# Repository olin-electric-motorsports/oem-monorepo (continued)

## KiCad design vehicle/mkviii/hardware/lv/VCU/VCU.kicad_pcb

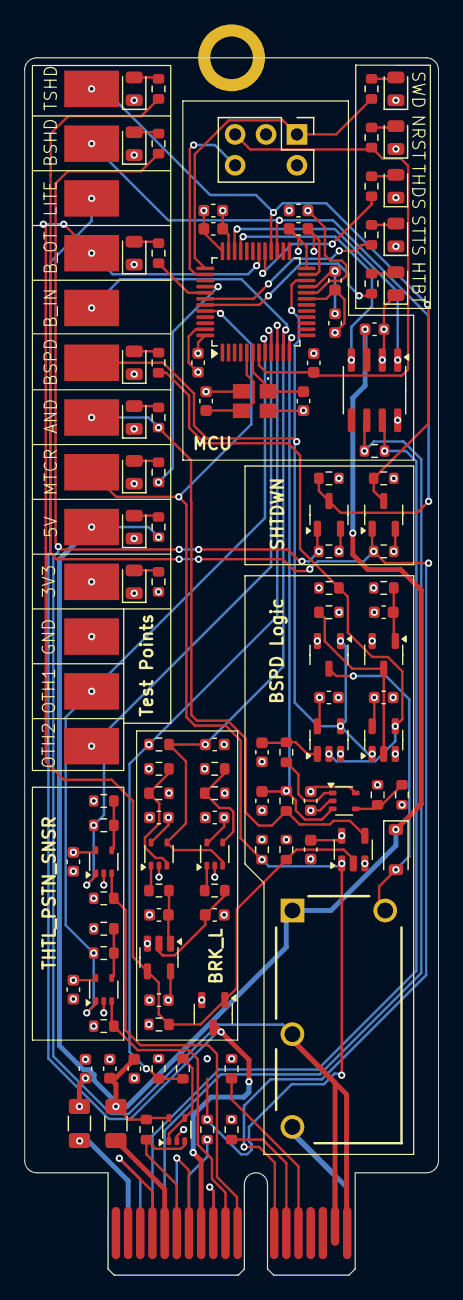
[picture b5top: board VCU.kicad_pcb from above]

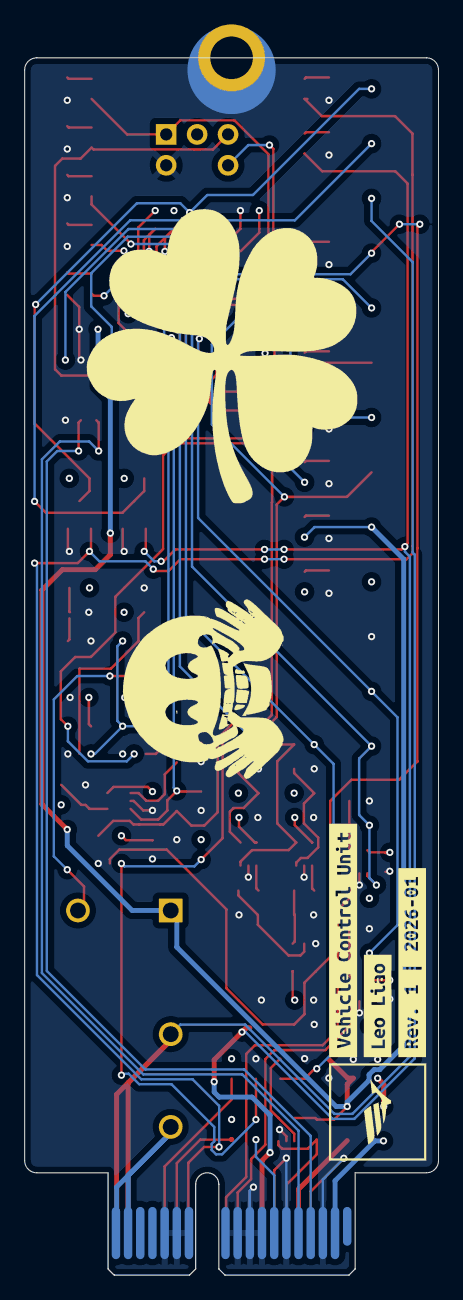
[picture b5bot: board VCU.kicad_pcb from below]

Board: 4 copper layers, 34.0 x 100.0 mm, 130 parts (3 on the bottom side), 69 nets.

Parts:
C1, C3, C5, C7, C9, C14, C15, C17, C19, C20, C21, C23, C24, C27, C28, C29: C_0.1uF; C_0603_1608Metric
C2: C_10nF; C_0603_1608Metric
C4, C18: C_1uF; C_0603_1608Metric
C6: C_4.7uF; C_0603_1608Metric
C8, C10: C_30pF; C_0603_1608Metric
C11, C26: C_0.1uF_16V; C_0603_1608Metric
C12, C13, C16: C_10uF_10V; C_0603_1608Metric
C22: C_0.22uF_50V; C_0603_1608Metric
C25: C_1uF_25V; C_0603_1608Metric
D1: MOTOR_ON; D_0805_2012Metric
D2: BRAKES; D_0805_2012Metric
D3: BSPD_TRIP; D_0805_2012Metric
D4: HEARTBEAT; D_0805_2012Metric
D5: THROTTLE_DISABLE; D_0805_2012Metric
D6: 5V; D_0805_2012Metric
D7: 3V3; D_0805_2012Metric
D8: NRST; D_0805_2012Metric
D9: SWDIO; D_0805_2012Metric
D10: D_Amber_LED; D_0805_2012Metric
D11: D_36V_500mW; D_SOD-123
D12: BSPD_TRIP_LED; D_0805_2012Metric
D13, D14: D_Blue_LED; D_0805_2012Metric
F1, F2: F_500mA_8V; Fuse_1206_3216Metric
H1: H_MountingHole
J1: J_Programming_Pin_Header; J_Programming_Pin_Header_Keyed
J2: J_PCIe_x1; J_PCIe_x1_Key
K1: K_10A_5V; G5Q1A4DC5 (K_SPST-NO_10A_5V_TH - G5Q-1A4-DC5)
Q1, Q2, Q3, Q4, Q5: SSM3K333R,LF; SOT-23-3
R1, R2, R3, R4, R5, R7, R8, R9, R12: R_200; R_0603_1608Metric
R6, R20, R27, R33: R_1k; R_0603_1608Metric
R10: R_120; R_0603_1608Metric
R11, R13, R17, R22, R23, R24, R26, R28, R32, R34, R35, R36, R39, R42: R_10k; R_0603_1608Metric
R14, R44, R47: R_0; R_0603_1608Metric
R16: R_5.1k; R_0603_1608Metric
R18, R19, R25, R38, R41: R_100k; R_0603_1608Metric
R21: R_71.5k; R_0603_1608Metric
R29: R_75k; R_0603_1608Metric
R30: R_576; R_0603_1608Metric
R31: R_100; R_0603_1608Metric
R37, R40: R_3k; R_0603_1608Metric
R43, R46: R_1M; R_0603_1608Metric
R45, R48: R_2.2k; R_0603_1608Metric
TP1: 5V; TP_Hook_SMD
TP2: 3V3; TP_Hook_SMD
TP3: GND; TP_Hook_SMD
TP4, TP5, TP6, TP7, TP8, TP9, TP10, TP11, TP12, TP13: TP_SMD; TP_Hook_SMD
U1: STM32G441CBT6; LQFP-48_7x7mm_P0.5mm
U2: MCP2561-E_SN; SOIC-8_3.9x4.9mm_P1.27mm
U3, U5, U8, U9, U11, U12: MCP6001T-I/LT; SOT-353_SC-70-5
U4: SN74LVC1G08DBVR; SOT-23-5
U6, U7: SN74LVC1G02DBVR; SOT-23-5
U10: SN74LVC1G32DBVR; SOT-23-5
Y1: X_16MHz_18pF; FA238160000MBC0 (X_16MHz_18pF_SMD - FA-238_16.0000MB-C0)
kibuzzard-6983BE89: G***; kibuzzard-6983BE89
kibuzzard-6983C564: G***; kibuzzard-6983C564
kibuzzard-6983C636: G***; kibuzzard-6983C636

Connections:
+3V3: C1.1, C2.1, C3.1, C4.1, C5.1, C6.1, C7.1, C13.1, C15.2, C17.1, C20.1, C21.1, C23.1, C24.1, C27.1, C28.1, C29.1, F2.1, J1.3, R7.1, R11.1, R12.1, R18.1, R22.1, R25.1, R26.1, R30.1, R32.1, R39.1, R42.1, R43.1, R46.1, TP2.1, U1.20 (VREF+), U1.21 (VDDA), U1.24 (VDD), U1.36 (VDD), U1.48 (VDD), U4.5 (VCC), U5.5 (V+), U6.5 (VCC), U7.5 (VCC), U8.5 (V+), U9.5 (V+), U10.5 (VCC), U11.5 (V+), U12.5 (V+)
+5V: C11.1, C12.1, C14.1, D11.1 (K), F1.1, K1.1, R6.1, R13.1, TP1.1, U2.3 (VDD), U3.5 (V+)
/BSPD/BRAKELIGHT_LL: Q3.1 (G), R19.1, R36.1, TP8.1, U1.30 ((EVENTOUT/SAI1_SCK_A/SAI1_CK2/TIM4_ETR/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), U4.2, U10.4
/BSPD/BSPD_LL: Q2.1 (G), TP6.1, U1.22 ((EVENTOUT/SAI1_SCK_A/TIM1_BKIN/LPUART1_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), U6.4, U7.1
/BSPD/BSPD_RELAY_IN: J2.A17 (SHDN_IN/io_22), J2.A18 (SHDN_IN/io_24), K1.3
/BSPD/BSPD_RELAY_OUT: J2.B17 (SHDN_OUT/io_23), J2.B18 (SHDN_OUT/io_25), K1.2, Q4.1 (G), R37.1, R38.1
/BSPD/MOTOR_CURRENT_SENSE: R14.2, R18.2, TP4.1, U1.44 ((EVENTOUT/LPTIM1_IN2/TIM3_CH4/COMP3_OUT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), U4.1
/BSPD/RC_TIMER_STATUS: C16.1, R21.2, U1.12 ((EVENTOUT/SAI1_FS_B/USART2_CK/SPI3_NSS/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), U5.3 (+)
/BrakeLight/BRAKELIGHT_CONN: J2.B8 (io_5), Q3.3 (D), TP9.1
/BrakeLight/BRAKE_PRESS_SENSE: R16.2, R17.1, R29.1, U1.10 ((EVENTOUT/UCPD1_FRSTX2/UCPD1_FRSTX1/LPU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)
/BrakeLight/BRAKE_PRESS_SENSE_FILTERED: C22.1, R29.2, TP7.1, U1.11 ((EVENTOUT/SAI1_MCLK_A/LPUART1_RX/TIM15_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), U8.4 (-), U9.3 (+)
/Microcontroller - STM32G441CBT6/5KW_LED: R1.1, U1.40 ((EVENTOUT/SAI1_SCK_B/TIM3_ETR/USART2_TX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)
/Microcontroller - STM32G441CBT6/BRAKE_LL_LED: R2.1, U1.41 ((EVENTOUT/SAI1_MCLK_B/TIM17_BKIN/USART2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)
/Microcontroller - STM32G441CBT6/BSPD_SHUTDOWN_SENSE: Q4.3 (D), R39.2, TP10.1, U1.27 ((EVENTOUT/LPUART1_CTS/USART3_NSS/USART3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)
/Microcontroller - STM32G441CBT6/BSPD_TRIP_LED: R3.1, U1.42 ((EVENTOUT/SAI1_SD_B/LPTIM1_IN1/TIM17_CH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)
/Microcontroller - STM32G441CBT6/CAN_+: J2.A4 (CAN+), R10.1, U2.7 (CANH)
/Microcontroller - STM32G441CBT6/CAN_-: J2.A5 (CAN-), R10.2, U2.6 (CANL)
/Microcontroller - STM32G441CBT6/CAN_RX: U1.33 ((EVENTOUT/TIM1_BKIN2/TIM1_CH4/TIM4_CH1/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), U2.4 (RXD)
/Microcontroller - STM32G441CBT6/CAN_TX: U1.34 ((EVENTOUT/TIM1_ETR/TIM4_CH2/FDCAN1_TX/C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), U2.1 (TXD)
/Microcontroller - STM32G441CBT6/HEARTBEAT_LED: R4.1, U1.43 ((EVENTOUT/SAI1_FS_B/LPTIM1_ETR/TIM8_BKI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)
/Microcontroller - STM32G441CBT6/NRST: C9.1, J1.4, R8.1, U1.7 ((EVENTOUT/RCC_MCO/GPIO_EXTI10)PG10-NRST)
/Microcontroller - STM32G441CBT6/OUTPUT_THROTTLE_1: R44.1, TP12.1, U1.8 ((EVENTOUT/TIM2_ETR/TIM8_ETR/TIM8_BKIN/C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), U11.1
/Microcontroller - STM32G441CBT6/OUTPUT_THROTTLE_2: R47.1, TP13.1, U1.9 ((EVENTOUT/TIM15_CH1N/USART2_DE/USART2_R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), U12.1
/Microcontroller - STM32G441CBT6/SS_INERTIA_OUTPUT: Q5.3 (D), R42.2, TP11.1, U1.28 ((EVENTOUT/COMP4_OUT/USART3_RTS/USART3_D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)
/Microcontroller - STM32G441CBT6/SWCLK: J1.5, U1.38 ((EVENTOUT/SAI1_FS_B/USART2_TX/TIM1_BKIN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)
/Microcontroller - STM32G441CBT6/SWDIO: J1.1, R9.1, U1.37 ((EVENTOUT/SAI1_SD_B/TIM4_CH3/USART3_NSS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)
/Microcontroller - STM32G441CBT6/THROTTLE_DISABLE: R5.1, U1.29 ((EVENTOUT/SPI2_MOSI/I2S2_SD/TIM1_CH3N/C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)
/PCIe x1 Connector/INPUT_THROTTLE_1: J2.B10 (io_9), R43.2, U11.3 (+)
/PCIe x1 Connector/INPUT_THROTTLE_2: J2.B11 (io_11), R46.2, U12.3 (+)
/PCIe x1 Connector/SS_INERTIA_SWITCH: J2.B12 (io_13), Q5.1 (G), R40.1, R41.1
/PCIe x1 Connector/THROTTLE_1+: J2.B13 (io_15), R11.2
/PCIe x1 Connector/THROTTLE_2+: J2.B14 (io_17), R12.2
GND: C1.2, C2.2, C3.2, C4.2, C5.2, C6.2, C7.2, C8.2, C9.2, C10.2, C11.2, C12.2, C13.2, C14.2, C15.1, C16.2, C17.2, C18.2, C19.1, C20.2, C21.2, C22.2, C23.2, C24.2, C25.2, C26.2, C27.2, C28.2, C29.2, D1.1 (K), D2.1 (K), D3.1 (K), D4.1 (K), D5.1 (K), D6.1 (K), D7.1 (K), D8.1 (K), D9.1 (K), D10.1 (K), D12.1 (K), D13.1 (K), D14.1 (K), H1.1, J1.2, J2.A3 (GND), J2.A6 (io_0), J2.A8 (io_4), J2.A9 (io_6), J2.A10 (io_8), J2.A11 (io_10), J2.A12 (io_12), J2.A13 (io_14), J2.A14 (io_16), J2.B4 (GND), J2.B7 (io_3), J2.B9 (io_7), Q1.2 (S), Q2.2 (S), Q3.2 (S), Q4.2 (S), Q5.2 (S), R17.2, R19.2, R23.2, R28.1, R31.2, R33.2, R36.2, R38.2, R41.2, R45.2, R48.2, TP3.1, U1.19 (VSSA), U1.23 (VSS), U1.35 (VSS), U1.47 (VSS), U2.2 (VSS), U2.8 (STBY), U3.2 (V-), U4.3 (GND), U5.2 (V-), U6.3 (GND), U7.3 (GND), U8.2 (V-), U9.2 (V-), U10.3 (GND), U11.2 (V-), U12.2 (V-), Y1.2, Y1.4
unnamed: C18.1, R24.2, U6.1
unnamed: C25.1, R34.2, U10.1
unnamed: C26.1, R35.2, U10.2
unnamed: D1.2 (A), R1.2
unnamed: D2.2 (A), R2.2
unnamed: D3.2 (A), R3.2
unnamed: D4.2 (A), R4.2
unnamed: D5.2 (A), R5.2
unnamed: D6.2 (A), R6.2
unnamed: D7.2 (A), R7.2
unnamed: D8.2 (A), R8.2
unnamed: D9.2 (A), R9.2
unnamed: D10.2 (A), R20.2
unnamed: D11.2 (A), K1.5, Q2.3 (D)
unnamed: D12.2 (A), R27.2
unnamed: D13.2 (A), R37.2
unnamed: D14.2 (A), R40.2
unnamed: F2.2, J2.A2 (3.3V)
unnamed: F1.2, J2.B5 (5V)
unnamed: J2.B6 (io_1), R13.2, U3.3 (+)
unnamed: J2.A7 (io_2), R14.1
unnamed: Q1.3 (D), R25.2, U7.2
unnamed: C19.2, Q1.1 (G), R26.2
unnamed: R20.1, R21.1, TP5.1, U4.4
unnamed: R24.1, U5.1
unnamed: R27.1, R28.2, U6.2, U7.4
unnamed: R34.1, U8.1
unnamed: R35.1, U9.1
unnamed: C8.1, U1.6 ((EVENTOUT/SPI2_SCK/I2S2_CK/GPIO_EXTI1)P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), Y1.1
unnamed: C10.1, U1.5 ((EVENTOUT/TIM1_CH3N/SPI2_NSS/I2S2_WS/I2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), Y1.3
unnamed: R16.1, U3.1, U3.4 (-)
unnamed: R22.2, R23.1, U5.4 (-)
unnamed: R32.2, R33.1, U8.3 (+)
unnamed: R30.2, R31.1, U9.4 (-)
unnamed: R44.2, R45.1, U11.4 (-)
unnamed: R47.2, R48.1, U12.4 (-)

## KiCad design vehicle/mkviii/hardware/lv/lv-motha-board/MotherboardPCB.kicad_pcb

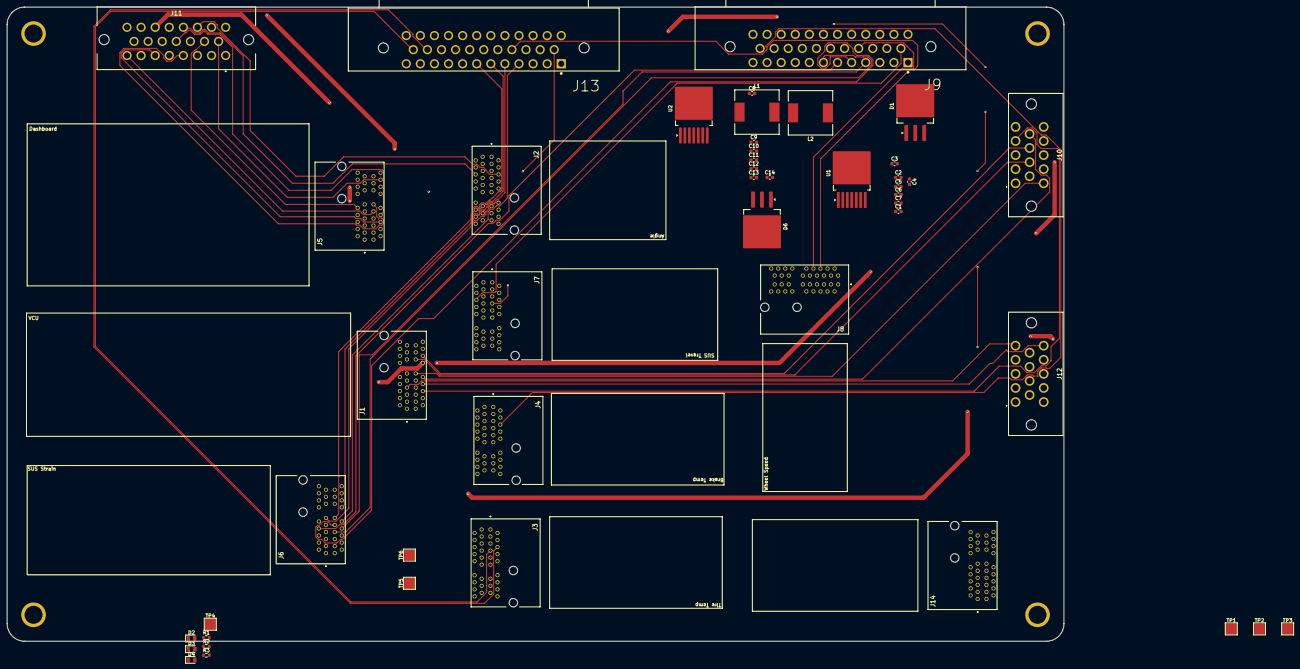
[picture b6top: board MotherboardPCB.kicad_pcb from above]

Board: 4 copper layers, 300.0 x 180.0 mm, 46 parts (0 on the bottom side), 55 nets.

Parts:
C1, C11: 0.47μF; C_0603_1608Metric
C2, C12: 0.01μF; C_0603_1608Metric
C3, C4, C13, C14: 180μF/16V; C_0603_1608Metric
C5, C6, C7, C8, C9, C10: 15μF/50V; C_0603_1608Metric
D1, D6: 6TQ045S; TO-263-3_TabPin2
D2, D3, D4: D_Blue_LED; LED_0805_2012Metric
J1, J2, J3, J4, J5, J6, J7, J8, J14: J_PCIe_x1
J9, J13: 776163-1; J_Ampseal_35_RA - 776163-1
J10, J12: J_Ampseal_14_RA
J11: J_Ampseal_23_RA
L1, L2: 22μH; L_12x12mm_H8mm
R1: 4.4 kΩ; R_0603_1608Metric
R2: 900 Ω; R_0603_1608Metric
R3: 150 Ω; R_0603_1608Metric
TP1, TP2, TP3, TP4, TP5, TP6: TestPoint; TestPoint_Pad_3.0x3.0mm
U1: LM2678SX-5.0/NOPB; TO-263-7_TabPin8
U2: LM2678SD-3.3/NOPB; TO-263-7_TabPin8

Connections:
+3V3: C13.1, C14.1, J1.A2 (12V/3V(DA_ONLY)), J2.A2 (12V/3V(DA_ONLY)), J3.A2 (12V/3V(DA_ONLY)), J4.A2 (12V/3V(DA_ONLY)), J5.A2 (12V/3V(DA_ONLY)), J6.A2 (12V/3V(DA_ONLY)), J7.A2 (12V/3V(DA_ONLY)), J8.A2 (12V/3V(DA_ONLY)), J9.2, J9.11, J9.19, J9.26, J10.2, J11.14, J13.2, J13.11, J13.18, J14.A2 (12V/3V(DA_ONLY)), L2.2, R3.1, TP3.1 (1_1), U2.7 (FB)
+5V: C2.2, C3.1, C4.1, D1.1 (K), J1.B5 (5V), J2.B5 (5V), J3.B5 (5V), J4.B5 (5V), J5.B5 (5V), J6.B5 (5V), J7.B5 (5V), J8.B5 (5V), J9.1, J9.10, J9.18, J9.25, J10.1, J11.13, J13.1, J13.10, J13.17, J14.B5 (5V), L1.1, L1.2, U1.1 (VSW), U1.6 (FB)
+BATT: C1.1, C5.1, C6.1, C7.1, C8.1, C9.1, C10.1, C11.1, J5.A11 (io_10), J11.1, J11.3, J11.5, J11.7, U1.2 (VIN), U2.2 (Vin), U2.3 (Vin)
/5V: R2.1, TP2.1 (1_1)
/12V: J9.14, J12.1, J13.14, R1.1, TP1.1 (1_1)
/AMS_LED_LOW_SIDE-: J5.B6 (io_1), J11.6
/BRAKELIGHT-: J1.B8 (io_5), J12.14
/BRAKE_PRESS_SENSE: J1.B6 (io_1), J10.4
/CAN_+: J1.A4 (CAN+), J2.A4 (CAN+), J3.A4 (CAN+), J4.A4 (CAN+), J5.A4 (CAN+), J6.A4 (CAN+), J7.A4 (CAN+), J8.A4 (CAN+), J9.21, J9.27, J11.17, J12.3, J12.6, J13.19, J14.A4 (CAN+), TP5.1 (1_1)
/CAN_-: J1.A5 (CAN-), J2.A5 (CAN-), J3.A5 (CAN-), J4.A5 (CAN-), J5.A5 (CAN-), J6.A5 (CAN-), J7.A5 (CAN-), J8.A5 (CAN-), J9.22, J9.28, J11.16, J12.4, J12.7, J13.20, J14.A5 (CAN-), TP6.1 (1_1)
/EXCITATION+_1: J6.B7 (io_3), J9.7
/EXCITATION+_2: J6.B10 (io_9), J13.4
/EXCITATION-_1: J6.A8 (io_4), J9.6
/EXCITATION-_2: J6.A11 (io_10), J13.5
/HV_LED_LOW_SIDE-: J5.B9 (io_7), J11.8
/IMD_LED_LOW_SIDE-: J5.B11 (io_11), J11.4
/IMU1_SIGNAL1: J9.30, J14.A6 (io_0)
/IMU1_SIGNAL2: J9.31, J14.B6 (io_1)
/IMU2_SIGNAL1: J9.32, J14.B7 (io_3)
/IMU2_SIGNAL2: J9.33, J14.A8 (io_4)
/IMU3_SIGNAL1: J9.34, J14.A9 (io_6)
/IMU3_SIGNAL2: J9.35, J14.B9 (io_7)
/INPUT_THROTTLE_1: J1.B10 (io_9), J10.9
/INPUT_THROTTLE_2: J1.B11 (io_11), J10.10
/IR_OUTPUT: J4.A6 (io_0), J9.23
/IR_SENSOR_SCL: J3.A6 (io_0), J13.22
/IR_SENSOR_SDA: J3.A7 (io_2), J13.23
/LIN_POTENTIOMETER_1: J7.B6 (io_1), J9.13
/LIN_POTENTIOMETER_2: J7.A7 (io_2), J13.13
/MOTOR_CURRENT_SENSE: J1.A7 (io_2), J12.5
/PWM_INPUT: J2.A6 (io_0), J11.18
/RTD_BUTTON_SENSE+: J5.B16 (io_21), J11.9
/RTD_BUTTON_SENSE-: J5.A10 (io_8), J11.10
/RTD_BUZZER_LOW_SIDE-: J5.B8 (io_5), J11.12
/SHDN_BOTS_IN: J5.A8 (io_4), J10.14
/SHDN_BOTS_OUT: J1.B12 (io_13), J10.13, J11.23
/SHDN_ESTOP_IN: J5.B10 (io_9), J11.21
/SHDN_ESTOP_OUT: J1.A17 (SHDN_IN/io_22), J1.A18 (SHDN_IN/io_24), J11.20, J12.11
/SHDN_OUT: J1.B17 (SHDN_OUT/io_23), J1.B18 (SHDN_OUT/io_25), J12.9
/SIGNAL+_1: J6.B9 (io_7), J9.5
/SIGNAL+_2: J6.B12 (io_13), J13.6
/SIGNAL-_1: J6.B8 (io_5), J9.4
/SIGNAL-_2: J6.B11 (io_11), J13.7
/STATUS_SIGNAL_INPUT: J2.B6 (io_1), J11.19
/THROTTLE_1+: J1.B13 (io_15), J10.7
/THROTTLE_2+: J1.B14 (io_17), J10.8
/WS1_VOUT: J8.B8 (io_5), J9.16
/WS2_VOUT: J8.B6 (io_1), J13.16
GND: C1.2, C3.2, C4.2, C5.2, C6.2, C7.2, C8.2, C9.2, C10.2, C11.2, C13.2, C14.2, D1.2 (A), D2.1 (K), D3.1 (K), D4.1 (K), D6.2 (A), J1.A3 (GND), J1.A6 (io_0), J1.A8 (io_4), J1.A9 (io_6), J1.A10 (io_8), J1.A11 (io_10), J1.A12 (io_12), J1.A13 (io_14), J1.A14 (io_16), J1.B4 (GND), J1.B7 (io_3), J1.B9 (io_7), J2.A3 (GND), J2.B4 (GND), J3.A3 (GND), J3.B4 (GND), J4.A3 (GND), J4.B4 (GND), J5.A3 (GND), J5.B4 (GND), J5.B14 (io_17), J6.A3 (GND), J6.A9 (io_6), J6.A10 (io_8), J6.A12 (io_12), J6.A13 (io_14), J6.B4 (GND), J7.A3 (GND), J7.A6 (io_0), J7.B4 (GND), J7.B7 (io_3), J8.A3 (GND), J8.B4 (GND), J9.3, J9.12, J9.15, J9.20, J9.29, J10.3, J10.5, J10.6, J11.2, J11.15, J12.2, J13.3, J13.12, J13.15, J13.21, J14.A3 (GND), J14.B4 (GND), TP4.1 (1_1), U1.4 (GND), U1.8 (TAB)
unnamed: D2.2 (A), R1.2
unnamed: D3.2 (A), R2.2
unnamed: D4.2 (A), R3.2
unnamed: C12.1, D6.1 (K), L2.1
unnamed: C2.1, U1.3 (CB)
unnamed: C12.2, U2.4 (BOOST)

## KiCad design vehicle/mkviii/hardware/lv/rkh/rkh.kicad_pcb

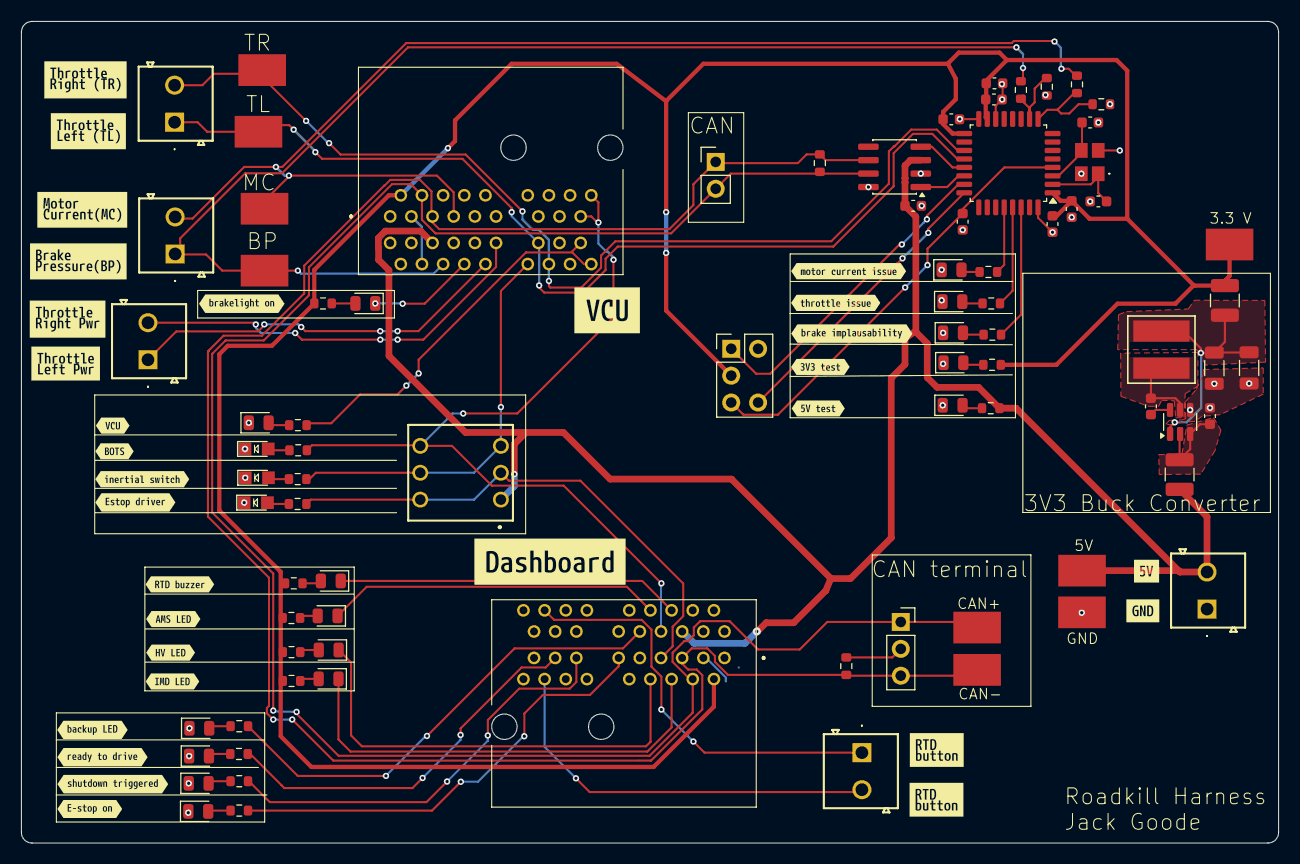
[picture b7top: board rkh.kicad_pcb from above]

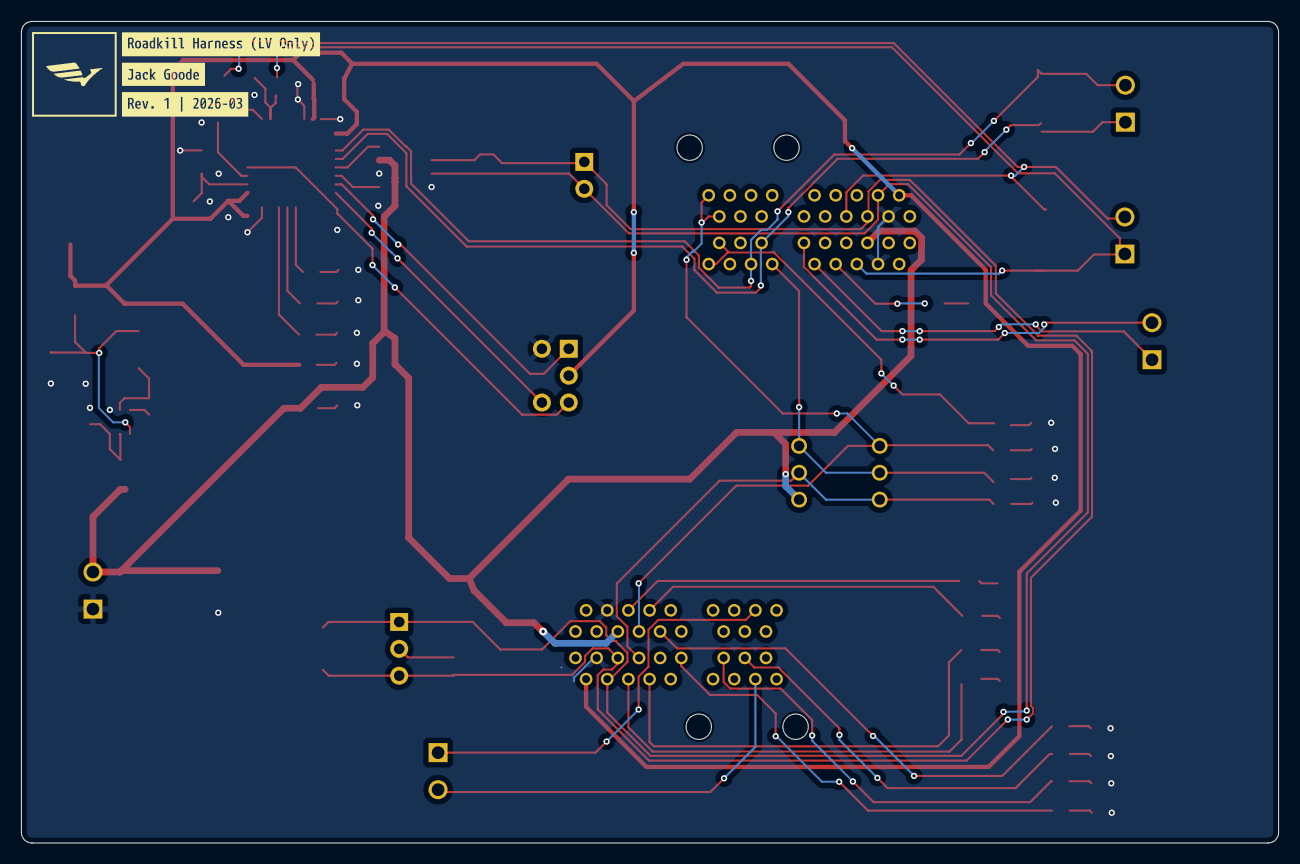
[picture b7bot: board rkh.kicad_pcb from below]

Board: 2 copper layers, 118.8 x 77.6 mm, 115 parts (3 on the bottom side), 61 nets.

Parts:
C1: C_10uF_10V; C_0603_1608Metric
C2, C4, C6, C10: C_0.1uF_16V; C_0603_1608Metric
C3, C12: C_22uF_25V; C_1206_3216Metric
C5: C_1uF_25V; C_0603_1608Metric
C7, C8: 30pF; C_0603_1608Metric
C9: C_4.7uF_25V; C_0603_1608Metric
C11: C_10nF_50V; C_0603_1608Metric
C13: 0u1F; C_0603
D1, D2, D3, D4, D5, D6, D7, D8, D9, D10, D12, D13, D14, D15, D16: LED; D_0805_2012Metric
D11, D19, D20: LED; LED_0805_OEM
Dashboard_PCIE1: pcie_x1; pcie_x_delete_asap
F1, F2: Fuse; Fuse_1210_3225Metric
J1, J2, J4, J6, J9: TWO_WIRE_SCREW_TERMINAL; wire_terminal_delete_asap
J3: J_PCIe_x1; pcie_x_delete_asap
J5: J_Programming_Pin_Header; J_Programming_Pin_Header_Keyed
J7: Conn_01x03_Pin; PinSocket_1x03_P2.54mm_Vertical
J8: Conn_01x02_Pin; PinHeader_1x02_P2.54mm_Vertical
L_3.9uH1: L; IND_BOURNS_SRR5018 (L_3.9uH_2A_55m_SMD)
R1, R2, R3, R4, R5, R6, R7, R8, R9, R11, R12, R15, R17, R18, R20, R21: R_1k_0.1W; R_0603_1608Metric
R10: R_120; R_0603
R16: R_120k; R_0603_1608Metric
R19: R_5k; R_0603_1608Metric
R22, R25: R__5k; R_0603_1608Metric
R23, R24: R_10k; R_0603_1608Metric
R26: R_120; R_0603_1608Metric
S1: DS01C-254-L-03BE; SW_DS01C254L03BE
TP1, TP2, TP3, TP4: TestPoint; test_point_delete_asap
TP5, TP6, TP7, TP8, TP9: TP_SMD; TP_Hook_SMD
U1: AP63203WU-7; SOT-23-6
U2: Roadkill_MCU; LQFP-32_7x7mm_P0.8mm
U4: MCP2561-E-SN; SOIC-8_3.9x4.9mm_P1.27mm
Y1: Crystal_16MHz_18pF; FA238160000MBC0 (X_16MHz_18pF_SMD - FA-238_16.0000MB-C0)
kibuzzard-69A0E4A7: G***; kibuzzard-69A0E4A7
kibuzzard-69A0E477: G***; kibuzzard-69A0E477
kibuzzard-69A764DF: G***; kibuzzard-69A764DF
kibuzzard-69A764E7: G***; kibuzzard-69A764E7
kibuzzard-69A764F6, kibuzzard-69A764F6#2: G***; kibuzzard-69A764F6
kibuzzard-69A766BA: G***; kibuzzard-69A766BA
kibuzzard-69A76600: G***; kibuzzard-69A76600
kibuzzard-69A76676: G***; kibuzzard-69A76676
kibuzzard-69A76791: G***; kibuzzard-69A76791
kibuzzard-69AA1B5D: G***; kibuzzard-69AA1B5D
kibuzzard-69AA1B51: G***; kibuzzard-69AA1B51
kibuzzard-69AA3EC3: G***; kibuzzard-69AA3EC3
kibuzzard-69AA3EDE: G***; kibuzzard-69AA3EDE
kibuzzard-69B8BF7C: G***; kibuzzard-69B8BF7C
kibuzzard-69B8BF88: G***; kibuzzard-69B8BF88
kibuzzard-69B8C0D1: G***; kibuzzard-69B8C0D1
kibuzzard-69B8C11E: G***; kibuzzard-69B8C11E
kibuzzard-69B8C173: G***; kibuzzard-69B8C173
kibuzzard-699FCAAF: G***; kibuzzard-699FCAAF
kibuzzard-699FCAF0: G***; kibuzzard-699FCAF0
kibuzzard-699FCB9F: G***; kibuzzard-699FCB9F
kibuzzard-699FCB70: G***; kibuzzard-699FCB70
kibuzzard-699FD2AF: G***; kibuzzard-699FD2AF
kibuzzard-699FD2CF: G***; kibuzzard-699FD2CF
kibuzzard-699FD2EF: G***; kibuzzard-699FD2EF
kibuzzard-699FD5DE: G***; kibuzzard-699FD5DE
kibuzzard-699FD9DF: G***; kibuzzard-699FD9DF
kibuzzard-699FD9F6: G***; kibuzzard-699FD9F6
kibuzzard-699FD92B: G***; kibuzzard-699FD92B
kibuzzard-699FD93E: G***; kibuzzard-699FD93E
kibuzzard-699FD307: G***; kibuzzard-699FD307
kibuzzard-699FD955: G***; kibuzzard-699FD955

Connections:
+3.3V: C4.2, C5.1, C9.1, C10.2, C11.1, Dashboard_PCIE1.A2 (3.3V), F2.2, J3.A2 (3.3V), J5.3, R1.1, R7.1, R11.1, R18.2, R20.1, R21.1, TP8.1, U2.1 (VDD), U2.15 (VDDA), U2.17 (VDD)
+5V: C13.1, Dashboard_PCIE1.B5 (5V), F1.1, J3.B5 (5V), J9.2, R17.2, S1.1 (COM_1), TP7.1, U4.3 (VDD)
/AMS_LED_LOW_SIDE: D16.1 (K), Dashboard_PCIE1.B8 (io_5)
/BACKUP_LED: Dashboard_PCIE1.B9 (io_7), R9.1
/BRAKE_IMPLAUSABILITY: R5.2, U2.30 ((TIM3_CH4/TIM4_CH2/TIM17_CH1N/GPIO_EXTI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)
/BRAKE_LIGHT: D1.1 (K), J3.B8 (io_5)
/BRAKE_PRESSURE: J3.B6 (io_1), J4.1, R25.2, TP1.1
/CAN_+: Dashboard_PCIE1.A4 (CAN+), J3.A4 (CAN+), J7.1, J8.2, R10.1, TP5.1, U4.7 (CANH)
/CAN_-: Dashboard_PCIE1.A5 (CAN-), J3.A5 (CAN-), J7.3, J8.1, R10.2, R16.1, TP6.1, U4.6 (CANL)
/CAN_RX: U2.21 ((FDCAN1_RX/GPIO_EXTI11)PA11), U4.4 (RXD)
/CAN_TX: U2.22 ((FDCAN1_TX/GPIO_EXTI12)PA12), U4.1 (TXD)
/E_STOP_ON: Dashboard_PCIE1.A11 (io_10), R2.1
/HV_LED_LOW_SIDE: D15.1 (K), Dashboard_PCIE1.A8 (io_4)
/IMD_LED_LOW_SIDE: D9.1 (K), Dashboard_PCIE1.A6 (io_0)
/MOTOR_CURRENT: J3.A7 (io_2), J4.2, R22.2, TP2.1
/MOTOR_CURRENT_ISSUE: R6.2, U2.28 ((TIM17_CH1/SPI1_MOSI/TIM3_CH2/TIM16_BKI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)
/NRST: C6.2, J5.4, U2.4 ((GPIO_EXTI10)PG10-NRST)
/READY_TO_DRIVE: Dashboard_PCIE1.A15 (io_18), R4.1
/RTD_BUZZER_LOW_SIDE: D12.1 (K), Dashboard_PCIE1.B6 (io_1)
/SHDN_IN_VCU: Dashboard_PCIE1.B7 (io_3), J3.A17 (SHDN_IN/io_22), J3.A18 (SHDN_IN/io_24), R26.2, S1.6 (NO_3)
/SHDN_OUT_VCU: J3.B17 (SHDN_OUT/io_23), J3.B18 (SHDN_OUT/io_25), R15.2
/SHUTDOWN_CIRCUIT_TRIGGERED: Dashboard_PCIE1.A13 (io_14), R3.1
/SS_ESTOP_DRIVER: Dashboard_PCIE1.A7 (io_2), R12.2, S1.2 (NO_1), S1.3 (COM_2)
/SS_INERTIA_SWITCH: J3.B12 (io_13), R19.2, S1.4 (NO_2), S1.5 (COM_3)
/SWCLK: J5.5, U2.24 ((SYS_JTCK-SWCLK/GPIO_EXTI14)PA14)
/SWDIO: J5.1, U2.23 ((SYS_JTMS-SWDIO/GPIO_EXTI13)PA13)
/THROTTLE_ISSUE: R8.2, U2.29 ((TIM4_CH1/TIM16_CH1N/GPIO_EXTI6)PB6)
/THROTTLE_L+: J2.1, J3.B13 (io_15), TP4.1, U2.20 ((TIM2_CH4/USART1_RX/TIM17_BKIN/GPIO_EXT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)
/THROTTLE_POWER_L: J3.B10 (io_9), J6.1
/THROTTLE_POWER_R: J3.B11 (io_11), J6.2
/THROTTLE_R+: J2.2, J3.B14 (io_17), TP3.1, U2.19 ((TIM2_CH3/TIM15_BKIN/USART1_TX/GPIO_EXT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)
GND: C1.2, C3.2, C4.1, C5.2, C6.1, C7.2, C8.2, C9.2, C10.1, C11.2, C12.2, C13.2, D2.1 (K), D3.1 (K), D4.1 (K), D5.1 (K), D6.1 (K), D7.1 (K), D8.1 (K), D10.1 (K), D11.1 (K), D13.1 (K), D14.1 (K), D19.1 (K), D20.1 (K), Dashboard_PCIE1.A3 (GND), Dashboard_PCIE1.B4 (GND), J3.A3 (GND), J3.B4 (GND), J5.2, J9.1, R23.1, R24.1, TP9.1, U1.4 (GND), U2.14 (VSSA), U2.16 (VSS), U2.32 (VSS), U4.2 (VSS), U4.8 (STBY), Y1.2, Y1.4
unnamed: D1.2 (A), R1.2
unnamed: D2.2 (A), R2.2
unnamed: D3.2 (A), R3.2
unnamed: D4.2 (A), R4.2
unnamed: D5.2 (A), R6.1
unnamed: D6.2 (A), R5.1
unnamed: D7.2 (A), R8.1
unnamed: D8.2 (A), R9.2
unnamed: D9.2 (A), R7.2
unnamed: D10.2 (A), R17.1
unnamed: D11.2 (A), R12.1
unnamed: D12.2 (A), R11.2
unnamed: D13.2 (A), R18.1
unnamed: D14.2 (A), R15.1
unnamed: D15.2 (A), R20.2
unnamed: D16.2 (A), R21.2
unnamed: D19.2 (A), R19.1
unnamed: D20.2 (A), R26.1
unnamed: Dashboard_PCIE1.A16 (io_20), J1.2
unnamed: Dashboard_PCIE1.B16 (io_21), J1.1
unnamed: J7.2, R16.2
unnamed: C2.1, U1.6 (BST)
unnamed: C1.1, F1.2, U1.2 (EN), U1.3 (VIN)
unnamed: C3.1, C12.1, F2.1, L_3.9uH1.2, U1.1 (FB)
unnamed: C2.2, L_3.9uH1.1, U1.5 (SW)
unnamed: R24.2, R25.1, U2.10 ((TIM2_ETR/TIM2_CH1/GPIO_EXTI5/ADC2_IN13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)
unnamed: R22.1, R23.2, U2.9 ((USART2_CK/TIM3_CH2/GPIO_EXTI4/ADC2_IN1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)
unnamed: C8.1, U2.2 (PF0-OSC_IN), Y1.1
unnamed: C7.1, U2.3 (PF1-OSC_OUT), Y1.3

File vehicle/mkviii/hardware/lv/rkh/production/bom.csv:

Designator,Footprint,Quantity,Value,LCSC Part #
C1,0603,1,C_10uF_10V,GRM188D71A106KA73D
"C10, C2, C4, C6",0603,4,C_0.1uF_16V,C0603C104Z4VACTU
C11,0603,1,C_10nF_50V,CL10B103KB8NNNC
"C12, C3",1206,2,C_22uF_25V,CL31A226KAHNNNE
C13,C_0603,1,0u1F,CL10B104KB8NNWC
C5,0603,1,C_1uF_25V,CL10B105KA8NNNC
"C7, C8",0603,2,30pF,CML0603C0G300JT50V
C9,0603,1,C_4.7uF_25V,GRM188R71E474KA12D
D1,0805,1,LED,
"D10, D12, D13, D14, D15, D16, D2, D3, D4, D5, D6, D7, D8, D9",0805,14,LED,LTST-C171KRKT
"D11, D19, D20",LED_0805_OEM,3,LED,
DASHBOARD_PCIE1,pcie_x_delete_asap,1,pcie_x1,2-1761465-1
"F1, F2",1210,2,Fuse,
"J1, J2, J4, J6, J9",wire_terminal_delete_asap,5,TWO_WIRE_SCREW_TERMINAL,
J3,pcie_x_delete_asap,1,J_PCIe_x1,2-1761465-1
J5,J_Programming_Pin_Header_Keyed,1,J_Programming_Pin_Header,
J7,PinSocket_1x03_P2.54mm_Vertical,1,Conn_01x03_Pin,
J8,PinHeader_1x02_P2.54mm_Vertical,1,Conn_01x02_Pin,
L_3.9UH1,IND_BOURNS_SRR5018 (L_3.9uH_2A_55m_SMD),1,L,
"R1, R11, R12, R15, R17, R18, R2, R20, R21, R3, R4, R5, R6, R7, R8, R9",0603,16,R_1k_0.1W,RMCF0603FT1K00 (or ERJ-3GEYJ102V)
R10,R_0603,1,R_120,RC0603FR-13120RL
R16,0603,1,R_120k,RMCF0603FT1K00 (or ERJ-3GEYJ102V)
R19,0603,1,R_5k,RMCF0603FT1K00 (or ERJ-3GEYJ102V)
"R22, R25",0603,2,R__5k,RMCF0603FT1K00 (or ERJ-3GEYJ102V)
"R23, R24",0603,2,R_10k,RMCF0603FT1K00 (or ERJ-3GEYJ102V)
R26,0603,1,R_120,RMCF0603FT1K00 (or ERJ-3GEYJ102V)
S1,SW_DS01C254L03BE,1,DS01C-254-L-03BE,
"TP1, TP2, TP3, TP4",test_point_delete_asap,4,TestPoint,
"TP5, TP6, TP7, TP8, TP9",TP_Hook_SMD,5,TP_SMD,5019
U1,SOT-23-6,1,AP63203WU-7,AP63203WU-7
U2,LQFP-32_7x7mm_P0.8mm,1,Roadkill_MCU,
U4,SOIC-8_3.9x4.9mm_P1.27mm,1,MCP2561-E-SN,
Y1,FA238160000MBC0 (X_16MHz_18pF_SMD - FA-238_16.0000MB-C0),1,Crystal_16MHz_18pF,7M-16.000MAAJ-T
